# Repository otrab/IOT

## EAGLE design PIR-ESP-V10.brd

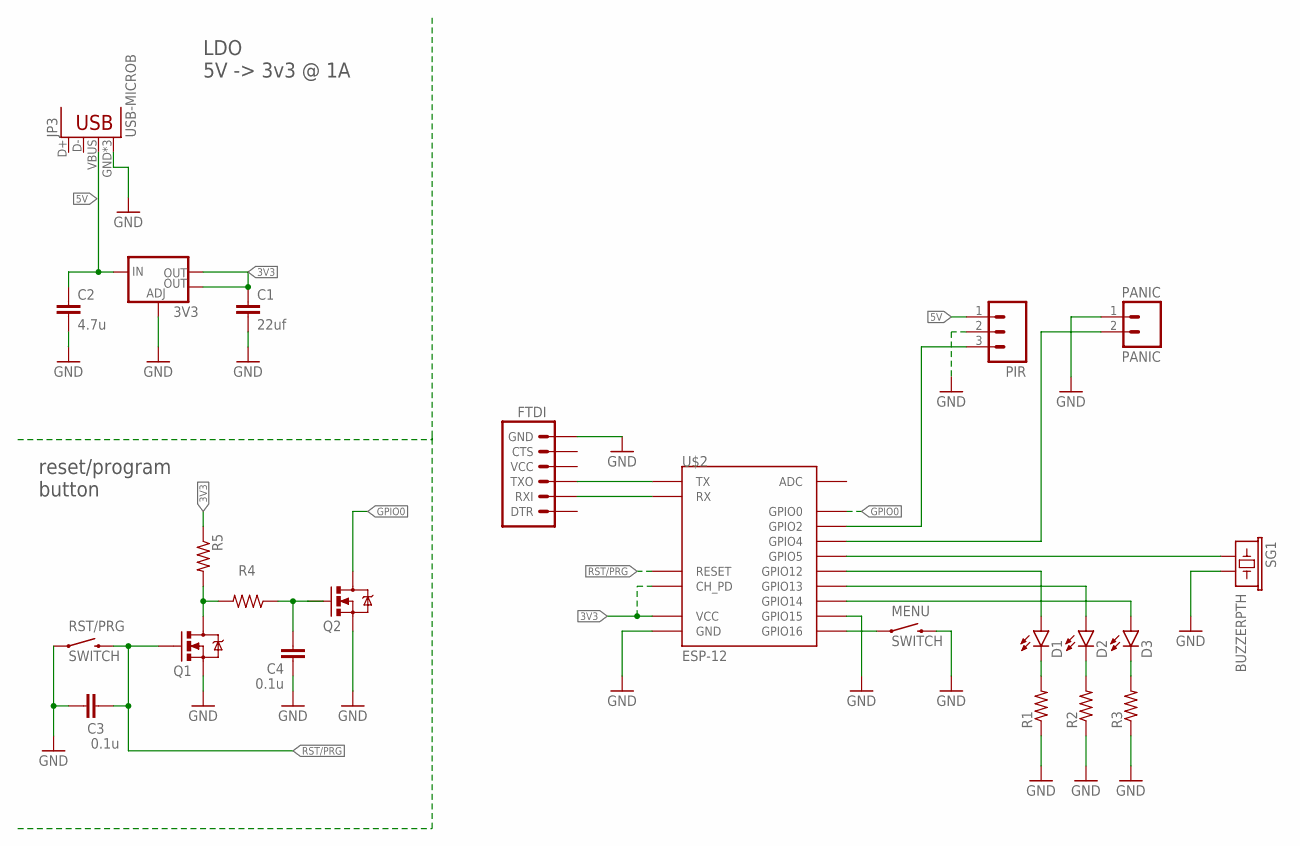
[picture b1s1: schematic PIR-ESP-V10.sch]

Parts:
3V3: V_REG_LM1117SOT223; SOT223
C1: 22uf; 1206
C2: 4.7u; 1206
C3, C4: 0.1u; 1206
D1, D2, D3: LED5MM
FTDI: ARDUINO_SERIAL_PROGRAMLOCK; 1X06_LOCK
JP3: USB-MICROB
MENU: SWITCH; TACTILE-PTH-SIDEEZ
PANIC: PANIC; 1X02_LONGPADS
PIR: M03LONGPADS; 1X03_LONGPADS
Q1, Q2: 200mA/50V; SOT23-3
R1, R2, R3, R4, R5: RESISTOR1206; 1206
RST/PRG: SWITCH; TACTILE-PTH-SIDEEZ
SG1: BUZZERPTH; BUZZER-12MM
U$2: ESP-12

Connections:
3V3: 3V3.2 (OUT), 3V3.4 (OUT), C1.1, R5.1, U$2.CH_PD, U$2.VCC
5V: 3V3.3 (IN), C2.1, JP3.VBUS, PIR.1
GND: 3V3.1 (ADJ), C1.2, C2.2, C3.1, C4.1, FTDI.6 (GND), JP3.GND, JP3.MT1 (GND), JP3.MT2 (GND), MENU.2, PANIC.1, PIR.2, Q1.2 (S), Q2.2 (S), R1.1, R2.1, R3.1, RST/PRG.1, SG1.- (2), U$2.GND, U$2.GPIO15
GPIO0: Q2.3 (D), U$2.GPIO0
unnamed: D1.A, U$2.GPIO12
unnamed: SG1.+ (1), U$2.GPIO5
unnamed: FTDI.3 (TXO), U$2.TX
unnamed: MENU.1, U$2.GPIO16
unnamed: FTDI.2 (RXI), U$2.RX
unnamed: D1.K (C), R1.2
unnamed: D2.K (C), R2.2
unnamed: D3.K (C), R3.2
unnamed: PANIC.2, U$2.GPIO4
unnamed: D2.A, U$2.GPIO13
unnamed: D3.A, U$2.GPIO14
unnamed: PIR.3, U$2.GPIO2
unnamed: C4.2, Q2.1 (G), R4.1
unnamed: Q1.3 (D), R4.2, R5.2
RST/PRG: C3.2, Q1.1 (G), RST/PRG.2, U$2.RESET

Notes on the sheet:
LDO 5V -> 3v3 @ 1A
reset/program button

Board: 2 copper layers, 23 parts (0 on the bottom side), 19 nets, no tracks yet.

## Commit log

2015-06-19 :tada: Added .gitattributes & .gitignore files
2015-06-19 borrador
2015-06-26 add wires

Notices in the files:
parts and their libraries:
SparkFun-Electromechanical: Licensing: Creative Commons ShareAlike 4.0 International - https://creativecommons.org/licenses/by-sa/4.0
